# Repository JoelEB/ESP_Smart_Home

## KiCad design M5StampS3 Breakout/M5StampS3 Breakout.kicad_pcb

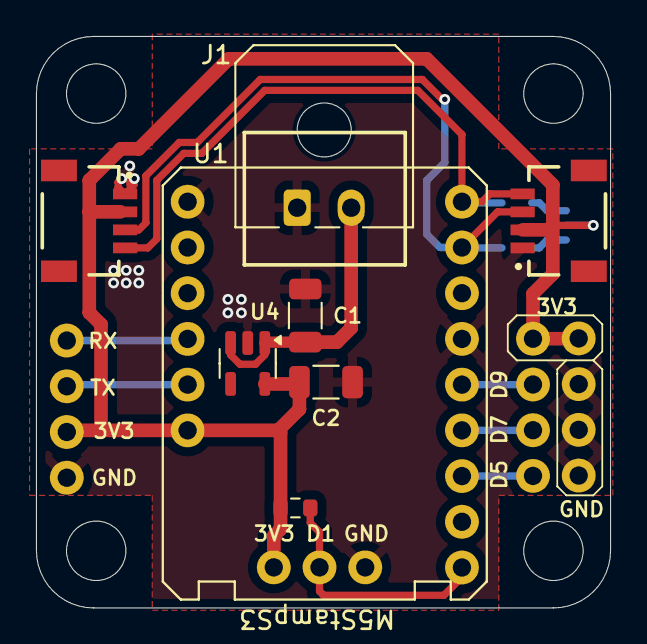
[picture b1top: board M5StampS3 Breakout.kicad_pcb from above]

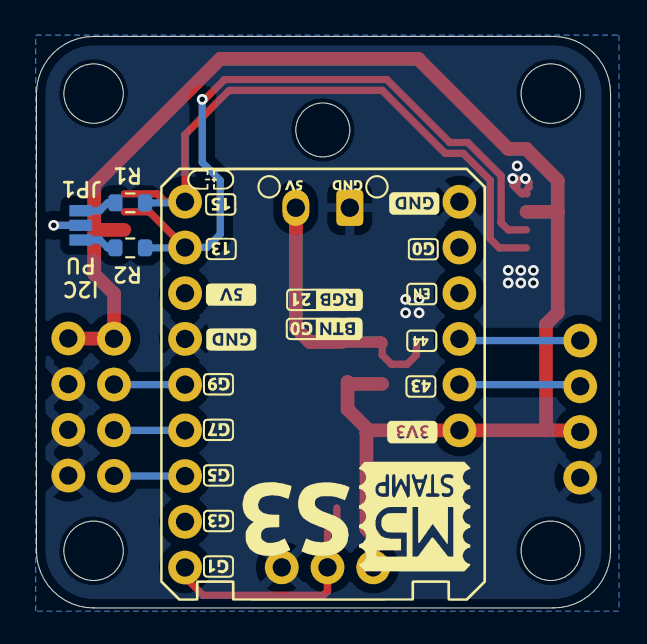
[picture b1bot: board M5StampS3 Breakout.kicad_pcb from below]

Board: 2 copper layers, 31.9 x 31.8 mm, 19 parts (3 on the bottom side), 13 nets.

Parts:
C1, C2: 10UF; C_1206_3216Metric
J1: Conn_01x02; Molex_Micro-Fit_3.0_43650-0200_1x02_P3.00mm_Horizontal
J2, J3: Qwiic_RA; JST04_1MM_RA
J4: Conn_01x03; 1X03
J5, J6, J7: Conn_01x04; 1X04
JP1: SolderJumper_3_Open; SMT-JUMPER_3_NO_NO-SILK
R1, R2, R3: 4.7k; R_0603_1608Metric
ST1, ST2, ST3, ST4: Stand_off; STAND-OFF
U1: M5StampS3; STAMP-S3-2_54-SOCKET
U4: XC6220B331MR; SOT-23-5

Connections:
+3.3V: C2.1, J2.2, J3.2, J4.3, J5.2, J6.1, J7.1, JP1.2 (C), R3.1, U1.15 (3V3), U4.5 (VOUT)
+12V: C1.1, J1.2, U4.1 (VIN), U4.3 (CE)
GND: C1.2, C2.2, J1.1, J2.1, J3.1, J4.1, J5.1, J7.2, J7.3, J7.4, U1.6 (GND), U1.10 (GND), U4.2 (GND)
GPIO1: J4.2, R3.2, U1.1 (A1CH0/TCH1/GPIO1)
GPIO5: J6.4, U1.3 (A1CH4/TCH5/GPIO5)
GPIO7: J6.3, U1.4 (A1CH6/TCH7/GPIO7)
GPIO9: J6.2, U1.5 (A1CH8/TCH9/GPIO9)
unnamed: JP1.1 (A), R2.2
unnamed: JP1.3 (B), R1.2
RX: J5.4, U1.13 (GPIO44/CLK2/RXD)
SCL: J2.4, J3.4, R2.1, U1.9 (A2CH4/TCH1/GPIO1/SCL)
SDA: J2.3, J3.3, R1.1, U1.8 (A2CH2/TCH13/GPIO13/SDA)
TX: J5.3, U1.14 (GPIO43/CLK1/TXD)

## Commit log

2024-08-25 Adding existing projects
2024-08-26 Minor Updates
2024-09-08 small update
